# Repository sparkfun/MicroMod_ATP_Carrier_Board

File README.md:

SparkFun MicroMod ATP Carrier Board
========================================

[*SparkFun MicroMod ATP Carrier Board (DEV-16885)*](https://www.sparkfun.com/products/16885)

<Basic description of the part.>

Repository Contents
-------------------

* **/Documentation** - Data sheets, additional product information
* **/Firmware** - Example code 
* **/Hardware** - Eagle design files (.brd, .sch)
* **/Production** - Production panel files (.brd)

Documentation
--------------
* **[Hookup Guide](https://learn.sparkfun.com/tutorials/micromod-all-the-pins-atp-carrier-board)** - Basic hookup guide

Product Versions
----------------
* [DEV-16885](https://www.sparkfun.com/products/16885)

Version History
---------------
* [v1.1](https://github.com/sparkfun/MicroMod_ATP_Carrier_Board/tree/v1.1) - Initial Release 

License Information
-------------------

This product is _**open source**_! 

Please review the LICENSE.md file for license information. 

If you have any questions or concerns on licensing, please contact technical support on our [SparkFun forums](https://forum.sparkfun.com/viewforum.php?f=152).

Distributed as-is; no warranty is given.

- Your friends at SparkFun.

_<COLLABORATION CREDIT>_

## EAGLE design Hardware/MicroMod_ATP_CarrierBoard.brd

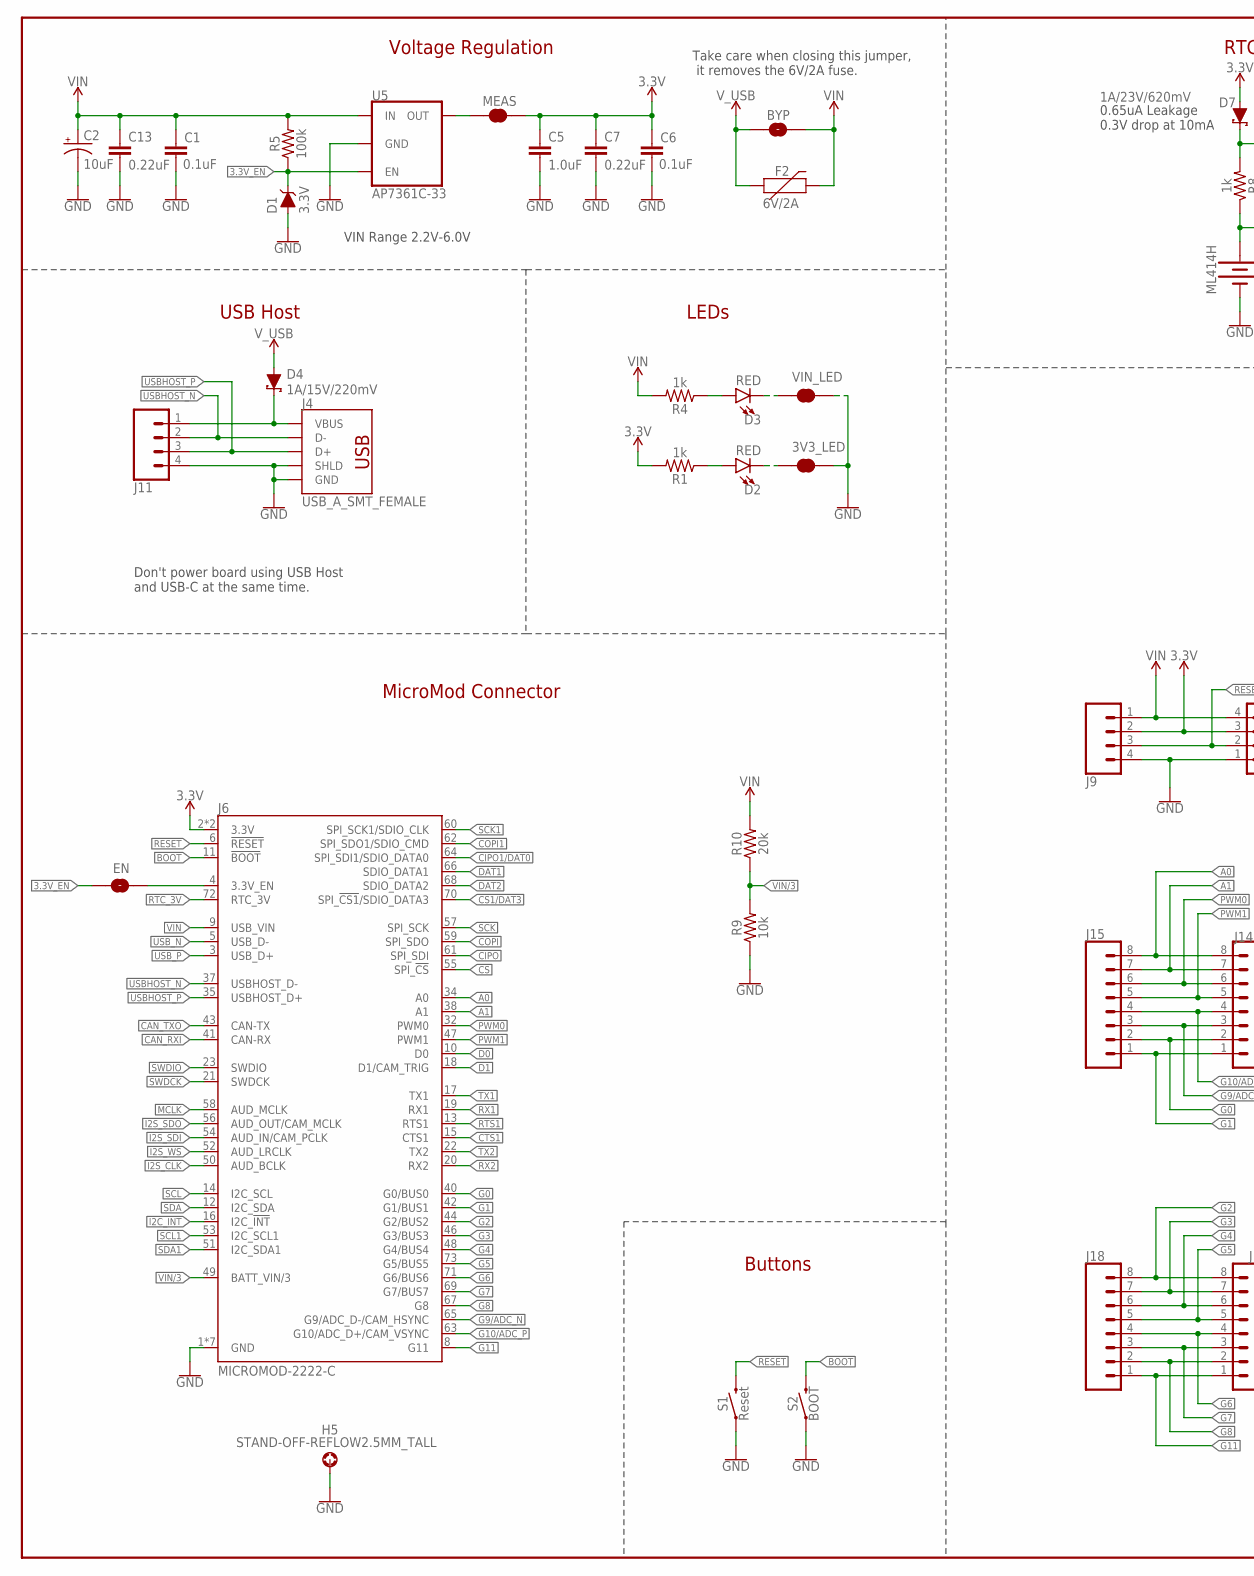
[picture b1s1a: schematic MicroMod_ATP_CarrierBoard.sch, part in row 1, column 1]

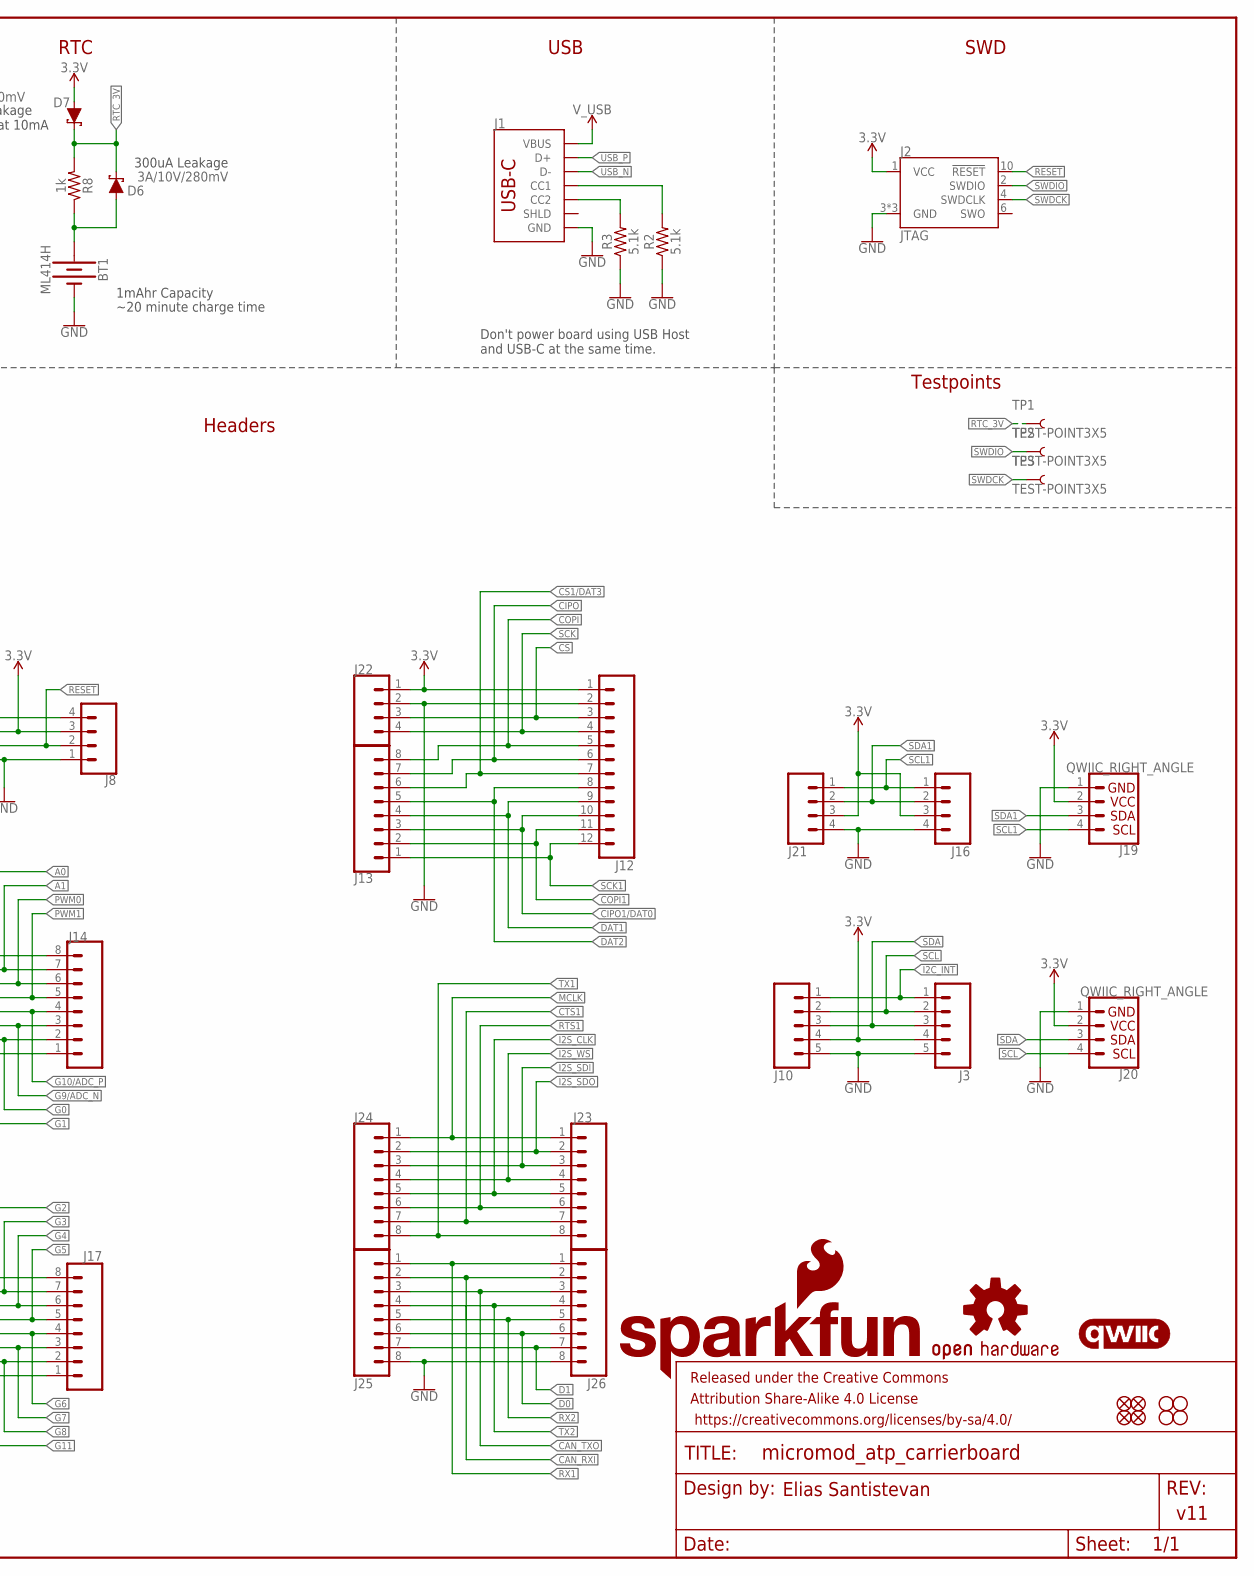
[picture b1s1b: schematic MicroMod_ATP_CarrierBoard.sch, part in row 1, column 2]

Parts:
3V3_LED: JUMPER-SMT_2_NC_TRACE_SILK; SMT-JUMPER_2_NC_TRACE_SILK
BT1: ML414H; ML414H_IV01E
BYP: JUMPER-SMT_2_NO_SILK; SMT-JUMPER_2_NO_SILK
C1, C6: 0.1uF; 0603
C2: 10uF; EIA3216
C5: 1.0uF; 0603
C7, C13: 0.22uF; 0603
D1: 3.3V; SOD-323
D2, D3: RED; LED-0603
D4: 1A/15V/220mV; DO-214BA
D6: 3A/10V/280mV; SOD-323
D7: 1A/23V/620mV; SOD-323
EN: JUMPER-SMT_2_NO_SILK; SMT-JUMPER_2_NO_SILK
F2: 6V/2A; 1210
FD1, FD2, FD3, FD4: FIDUCIALUFIDUCIAL; FIDUCIAL-MICRO
FRAME1: FRAME-LEDGER; CREATIVE_COMMONS
H1, H2, H3, H4: STAND-OFF
H5: STAND-OFF-REFLOW2.5MM_TALL; STAND-OFF-REFLOW-M2.5
J1: USB_C_2-LAYER_PADS; USB-C-16P-2LAYER-PADS
J2: JTAG; 2X5-PTH-1.27MM
J3: CONN_05NO_SILK; 1X05_NO_SILK
J4: USB_A_SMT_FEMALE; USB-A-S-SILK-FEMALE
J6: MICROMOD-2222-C; M.2-CONNECTOR-E
J8, J21: 1X04_SMD_STRAIGHT_COMBO; 1X04_SMD_VERTICAL_COMBO
J9: CONN_041X04_NO_SILK; 1X04_NO_SILK
J10: CONN_05VERT_FEMALE_HEADER; 1X05_SMD_VERTICAL_COMBO
J11, J16, J22: CONN_041X04_NO_SILK_NO_POP; 1X04_NO_SILK
J12: CONN_12SMD_COMBINED; 1X12_SMD_COMBINED
J13: CONN_08NO_SILK_DNP; 1X08_NO_SILK
J14, J17, J24, J25: CONN_08SMD-COMBO-FEMALE; 1X08_SMD_COMBINED
J15, J18, J23, J26: CONN_08NO_SILK_FEMALE_PTH; 1X08_NO_SILK
J19, J20: QWIIC_RIGHT_ANGLE; JST04_1MM_RA
LOGO1: SFE_LOGO_NAME_FLAME.1_INCH; SFE_LOGO_NAME_FLAME_.1
LOGO2: QWIIC_LOGO_5MM; QWIIC_5MM
LOGO3: OSHW-LOGOMINI; OSHW-LOGO-MINI
MEAS: JUMPER-COMBO_2_NC_TRACE; COMBO-JUMPER_2_NC_TRACE
R1, R4, R8: 1k; 0603
R2, R3: 5.1k; 0603
R5: 100k; 0603
R9: 10k; 0603
R10: 20k; 0603
S1: Reset; TACTILE_SWITCH_SMD_5.2MM
S2: BOOT; TACTILE_SWITCH_SMD_5.2MM
TP1, TP2, TP3: TEST-POINT3X5; PAD.03X.05
U5: AP7361C-33; UDFN-8
VIN_LED: JUMPER-SMT_2_NC_TRACE_SILK; SMT-JUMPER_2_NC_TRACE_SILK

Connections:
3.3V: C5.1, C6.1, C7.1, D7.A, J2.1 (VCC), J3.4, J6.2 (3.3V), J6.74 (3.3V), J8.3, J9.2, J10.4, J12.1, J16.3, J19.2, J20.2, J21.3, J22.1, MEAS.2, MEAS.4 (2), R1.2
3.3V_EN: D1.C, EN.1, R5.1, U5.5 (EN)
!BOOT!: J6.11 (!BOOT!), S2.3 (2), S2.4 (2)
!CS1!/DAT3: J6.70 (SPI_!CS1!/SDIO_DATA3), J12.7, J13.6
!CS!: J6.55 (SPI_!CS!), J12.3, J22.3
!RESET: J2.10 (!RESET), J6.6 (!RESET!), J8.2, J9.3, S1.3 (2), S1.4 (2)
A0: J6.34 (A0), J14.8, J15.8
A1: J6.38 (A1), J14.7, J15.7
CAN_RXI: J6.41 (CAN-RX), J25.2, J26.2
CAN_TXO: J6.43 (CAN-TX), J25.3, J26.3
CIPO: J6.61 (SPI_SDI), J12.6, J13.7
CIPO1/DAT0: J6.64 (SPI_SDI1/SDIO_DATA0), J12.10, J13.3
COPI: J6.59 (SPI_SDO), J12.5, J13.8
COPI1: J6.62 (SPI_SDO1/SDIO_CMD), J12.11, J13.2
CTS1: J6.15 (CTS1), J23.7, J24.7
D0: J6.10 (D0), J25.6, J26.6
D1: J6.18 (D1/CAM_TRIG), J25.7, J26.7
DAT1: J6.66 (SDIO_DATA1), J12.9, J13.4
DAT2: J6.68 (SDIO_DATA2), J12.8, J13.5
G0: J6.40 (G0/BUS0), J14.2, J15.2
G1: J6.42 (G1/BUS1), J14.1, J15.1
G2: J6.44 (G2/BUS2), J17.8, J18.8
G3: J6.46 (G3/BUS3), J17.7, J18.7
G4: J6.48 (G4/BUS4), J17.6, J18.6
G5: J6.73 (G5/BUS5), J17.5, J18.5
G6: J6.71 (G6/BUS6), J17.4, J18.4
G7: J6.69 (G7/BUS7), J17.3, J18.3
G8: J6.67 (G8), J17.2, J18.2
G9/ADC_N: J6.65 (G9/ADC_D-/CAM_HSYNC), J14.3, J15.3
G10/ADC_P: J6.63 (G10/ADC_D+/CAM_VSYNC), J14.4, J15.4
G11: J6.8 (G11), J17.1, J18.1
GND: 3V3_LED.2, BT1.-, C1.2, C2.-, C5.2, C6.2, C7.2, C13.2, D1.A, H5.1, J1.GND, J1.GND2 (GND), J2.3 (GND), J2.5 (GND), J2.9 (GND), J3.5, J4.GND, J4.SHLD1 (SHLD), J4.SHLD2 (SHLD), J6.1 (GND), J6.7 (GND), J6.33 (GND), J6.36 (GND), J6.39 (GND), J6.45 (GND), J6.75 (GND), J8.1, J9.4, J10.5, J11.4, J12.2, J16.4, J19.1, J20.1, J21.4, J22.2, J25.8, J26.8, R2.1, R3.1, R9.1, S1.1, S1.2 (1), S2.1, S2.2 (1), U5.4 (GND), U5.EP (GND), VIN_LED.2
I2C_!INT: J3.1, J6.16 (I2C_!INT!), J10.1
I2S_CLK: J6.50 (AUD_BCLK), J23.5, J24.5
I2S_SDI: J6.54 (AUD_IN/CAM_PCLK), J23.3, J24.3
I2S_SDO: J6.56 (AUD_OUT/CAM_MCLK), J23.2, J24.2
I2S_WS: J6.52 (AUD_LRCLK), J23.4, J24.4
MCLK: J6.58 (AUD_MCLK), J23.1, J24.1
unnamed: D2.A, R1.1
unnamed: D3.A, R4.1
unnamed: 3V3_LED.1, D2.C
unnamed: D3.C, VIN_LED.1
unnamed: EN.2, J6.4 (3.3V_EN)
unnamed: D4.C, J4.VBUS, J11.1
unnamed: J1.A5 (CC1), R2.2
unnamed: J1.B5 (CC2), R3.2
unnamed: BT1.+, D6.A, R8.1
OUT_MEAS: MEAS.1, MEAS.3 (1), U5.1 (OUT)
PWM0: J6.32 (PWM0), J14.6, J15.6
PWM1: J6.47 (PWM1), J14.5, J15.5
RTC_3V: D6.C, D7.C, J6.72 (RTC_3V), R8.2, TP1.P$1
RTS1: J6.13 (RTS1), J23.6, J24.6
RX1: J6.19 (RX1), J25.1, J26.1
RX2: J6.20 (RX2), J25.5, J26.5
SCK: J6.57 (SPI_SCK), J12.4, J22.4
SCK1: J6.60 (SPI_SCK1/SDIO_CLK), J12.12, J13.1
SCL: J3.2, J6.14 (I2C_SCL), J10.2, J20.4
SCL1: J6.53 (I2C_SCL1), J16.1, J19.4, J21.1
SDA: J3.3, J6.12 (I2C_SDA), J10.3, J20.3
SDA1: J6.51 (I2C_SDA1), J16.2, J19.3, J21.2
SWDCK: J2.4 (SWDCLK), J6.21 (SWDCK), TP3.P$1
SWDIO: J2.2 (SWDIO), J6.23 (SWDIO), TP2.P$1
TX1: J6.17 (TX1), J23.8, J24.8
TX2: J6.22 (TX2), J25.4, J26.4
USBHOST_N: J4.D-, J6.37 (USBHOST_D-), J11.2
USBHOST_P: J4.D+, J6.35 (USBHOST_D+), J11.3
USB_N: J1.A7 (D-), J1.B7 (D-), J6.5 (USB_D-)
USB_P: J1.A6 (D+), J1.B6 (D+), J6.3 (USB_D+)
VIN: BYP.2, C1.1, C2.+, C13.1, F2.2, J6.9 (USB_VIN), J8.4, J9.1, R4.2, R5.2, R10.2, U5.8 (IN)
VIN/3: J6.49 (BATT_VIN/3), R9.2, R10.1
V_USB: BYP.1, D4.A, F2.1, J1.VBUS1 (VBUS), J1.VBUS2 (VBUS)

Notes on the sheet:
300uA Leakage
0.65uA Leakage 0.3V drop at 10mA
~20 minute charge time
1mAhr Capacity
Take care when closing this jumper, it removes the 6V/2A fuse.
SWD
USB
Headers
RTC
Voltage Regulation
MicroMod Connector
Elias Santistevan
LEDs
USB Host
Buttons
v11
VIN Range 2.2V-6.0V
Don't power board using USB Host and USB-C at the same time.
Testpoints

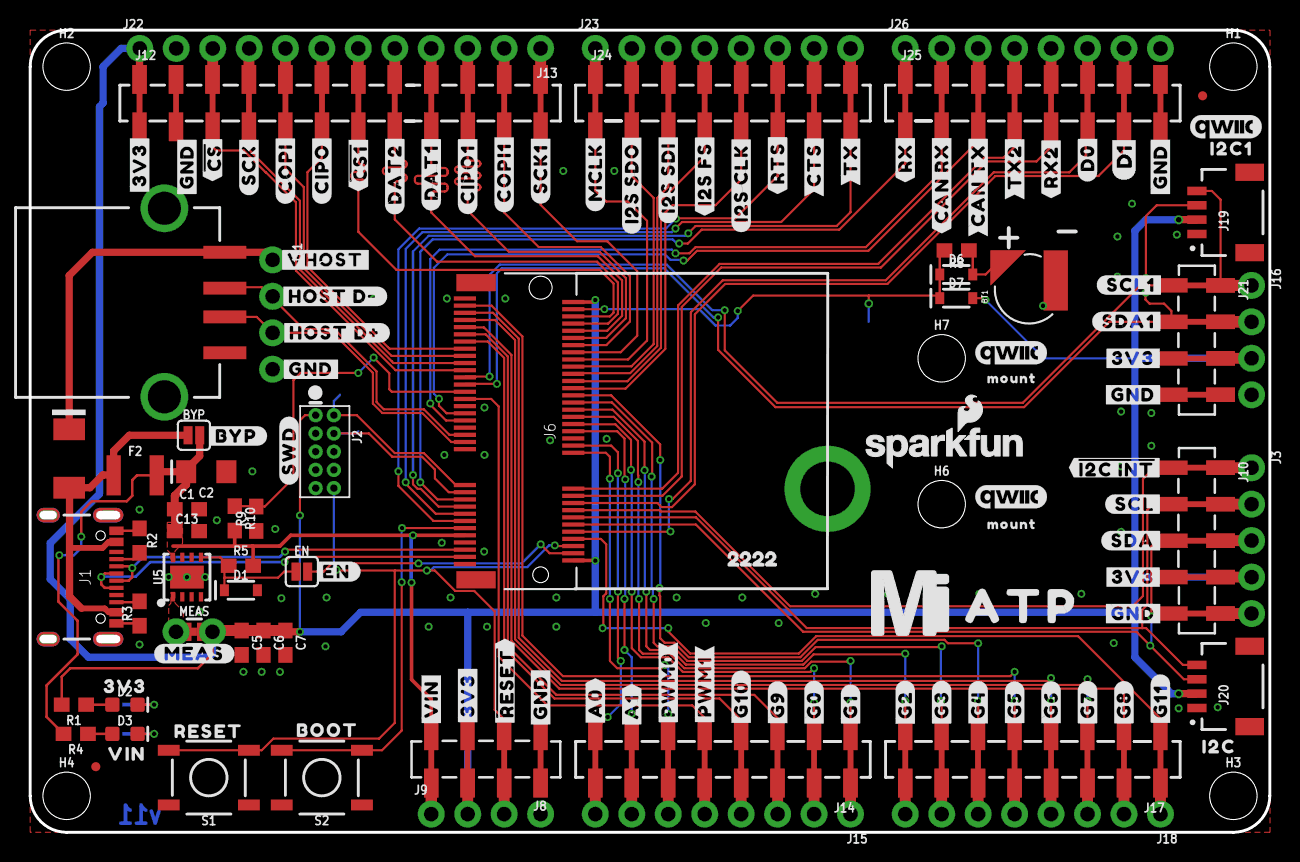
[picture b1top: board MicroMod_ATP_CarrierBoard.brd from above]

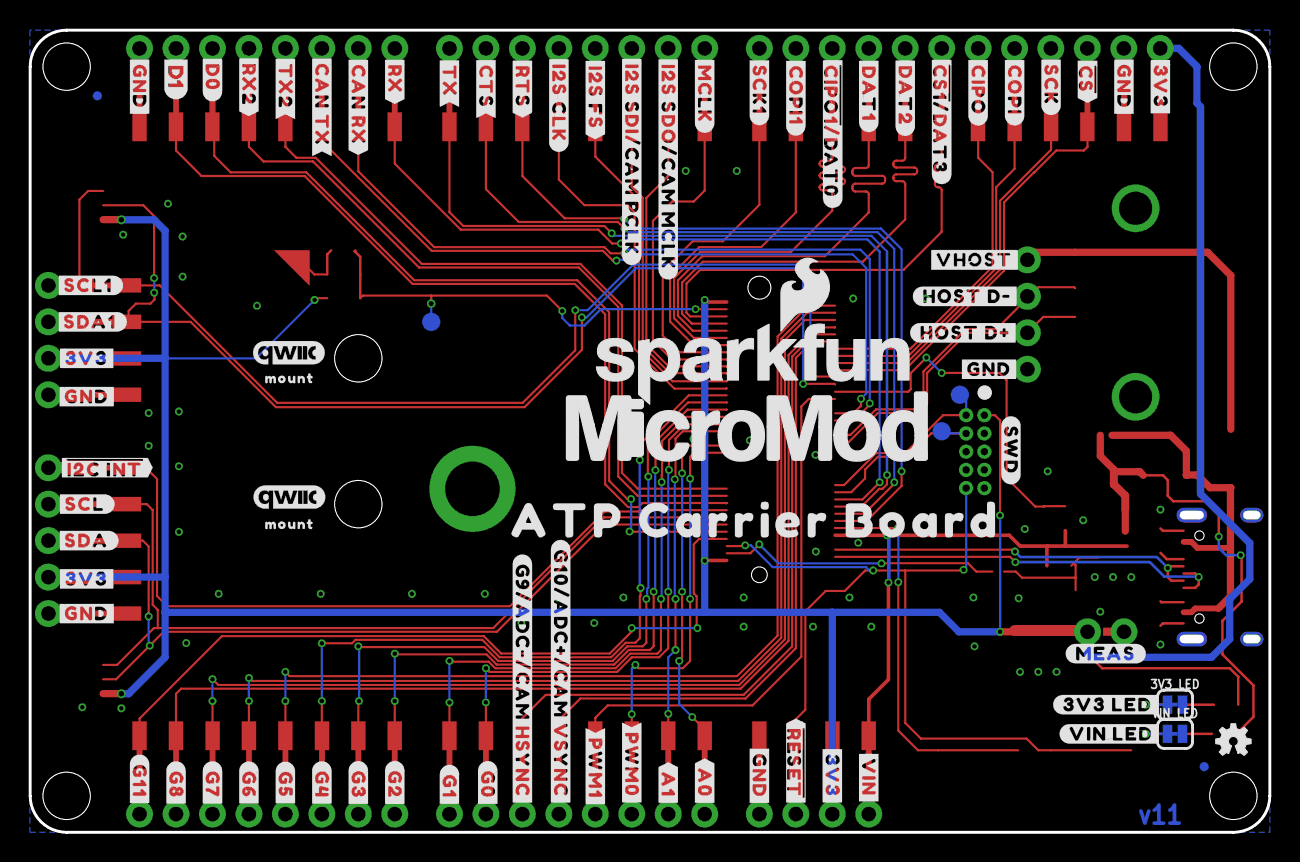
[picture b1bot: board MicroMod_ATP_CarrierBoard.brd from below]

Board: 2 copper layers, 86.4 x 55.9 mm, 222 parts (80 on the bottom side), 71 nets.

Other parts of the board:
H6, H7: STAND-OFF
LOGO4: SFE_LOGO_NAME_FLAME.2_INCH; SFE_LOGO_NAME_FLAME_.2
LOGO5, LOGO6, LOGO7, LOGO8: QWIIC_LOGO_3MM; QWIIC_5MM
U$1, U$123: #A0#10
U$2, U$124: #A1#10
U$3, U$27, U$46, U$47, U$58, U$89, U$100, U$101, U$102, U$103, U$104, U$105: #GND#0
U$4, U$120: #G0#2
U$5: #RESET10
U$6, U$98: #D0#0
U$7, U$119: #G1#2
U$8, U$118: #G2#2
U$9, U$117: #G3#3
U$10, U$116: #G4#4
U$11, U$115: #G5#5
U$12, U$114: #G6#6
U$13, U$113: #G7#7
U$14, U$112: #G8#8
U$15: #G9#9
U$16: #G10#10
U$17, U$111: #G11#10
U$18, U$121: #PWM0#10
U$19, U$122: #PWM1#10
U$20: ##CS1##5178039
U$21, U$110: ##I2C_INT##10
U$22: #CAN_RX#9
U$23, U$97: #CAN_TX#10
U$24: #CIPO#3
U$25: #COPI#2
U$26: #CTS#6
U$28: #SCK#2
U$29: #I2S_FS#5
U$30: #I2S_SDI#5
U$31: #I2S_SDO#5
U$32: #MCLK#4
U$33: #RTS#5
U$34: #RX#8
U$35: #TX#7
U$36: #DAT1#5178039
U$37, U$125: ##RESET##7
U$38, U$60, U$61, U$70, U$88, U$106, U$107, U$126: #3V3#1
U$39: #BYP#8
U$40, U$128: #HOST_D##9
U$41, U$129: #HOST_D##10
U$42, U$132: #MEAS#10
U$43: BOOT10
U$44, U$108: #SDA#4
U$45, U$127: #VIN#6
U$48: #EN#0
U$49, U$109: #SCL#5
U$50, U$146: #VHOST#0
U$51, U$131: #SWD#10
U$52: #I2S_CLK#5
U$53: #DAT2#5178039
U$54: #CIPO1#5178039
U$55: 22229
U$56: ##CIPO1##DAT0#5178038
U$57, U$75: #COPI1#2
U$59: ##CS##0
U$62: ATP0
U$63, U$76: #RX2#3
U$64, U$80: #TX2#2
U$65, U$78: #SCL1#3
U$66, U$79: #SDA1#3
U$67, U$77: #SCK1#2
U$68: VIN3
U$69: 3V34
U$71: I2C4
U$72: I2C14
U$73: ATP_CARRIER_BOARD1
U$81: ##CS##5178037
U$82: #DAT2#5
U$83: #DAT1#5
U$84: ##CS1##DAT3#5178037
U$85: #COPI#4
U$86: #SCK#4
U$87: #MCLK#6
U$90: #I2S_FS#7
U$91: #I2S_CLK#7
U$92: #RTS#7
U$93: #CTS#8
U$94: #TX#9
U$95: #RX#10
U$96: #CAN_RX#10
U$99, U$145: D10
U$133: #VIN_LED#10
U$134: #3V3_LED#10
U$135: #G9#ADC##CAM_HSYNC#9
U$136: #G10#ADC##CAM_VSYNC#10
U$137: #I2S_SDI#CAM_PCLK#7
U$138: #I2S_SDO#CAM_MCLK#7
U$139, U$141, U$142, U$143: MOUNT10
U$140: MICROMOD_MI_LOGO_1
U$144: MICROMOD_LOGO_1
U$147: #CIPO#5178038

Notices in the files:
parts and their libraries:
SparkFun-Aesthetics: Licensing: Creative Commons ShareAlike 4.0 International - https://creativecommons.org/licenses/by-sa/4.0
SparkFun-Aesthetics: Released under the Creative Commons Attribution Share-Alike 4.0 License
SparkFun-Aesthetics: https://creativecommons.org/licenses/by-sa/4.0
